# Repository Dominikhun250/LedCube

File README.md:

# LedCube
Self made pcb for a small cube lamp. Where you can set the color of the leds & the lamp.
Its a DIY project.

## Screenshots

## Credits
Original project: [AirCube](https://github.com/StuckAtPrototype/AirCube)
Pcb & Case made by: [Dominikhun250](https://github.com/Dominikhun250)

## License

[Apache License](https://github.com/Dominikhun250/LedCube/blob/main/LICENSE)

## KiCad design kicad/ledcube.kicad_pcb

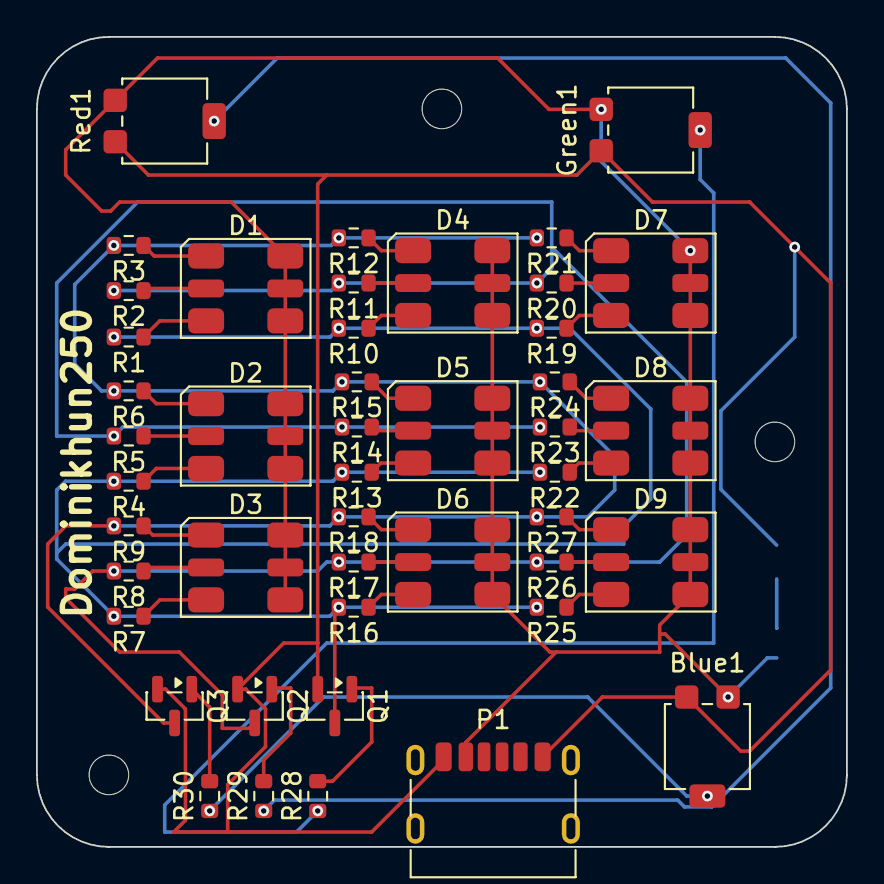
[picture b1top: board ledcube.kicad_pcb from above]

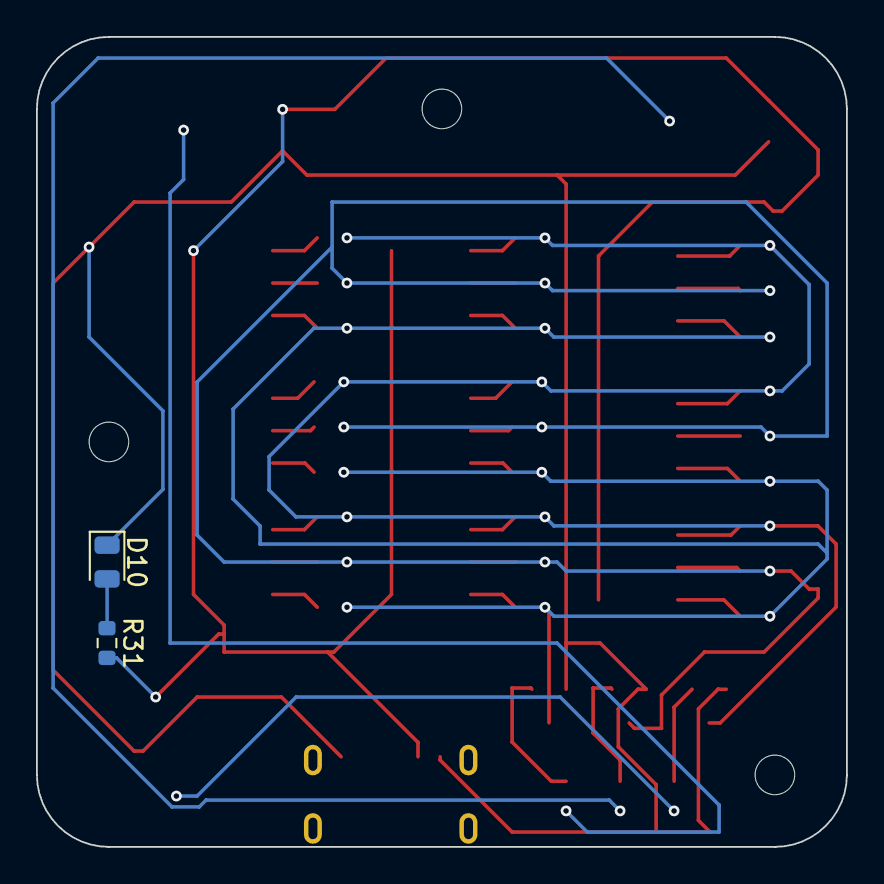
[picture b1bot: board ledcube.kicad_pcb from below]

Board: 2 copper layers, 45.0 x 45.0 mm, 48 parts (2 on the bottom side), 39 nets.

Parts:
Blue1: R_Potentiometer_Trim; Potentiometer_Bourns_3314G_Vertical
D1, D2, D3, D4, D5, D6, D7, D8, D9: Inolux_IN-P55TATRGB; LED_Inolux_IN-P55TATRGB_PLCC6_5.0x5.5mm_P1.8mm
D10: LED; LED_0805_2012Metric
Green1: R_Potentiometer_Trim; Potentiometer_Bourns_3314G_Vertical
P1: USB_C_Plug_USB2.0; USB_C_Receptacle_HRO_TYPE-C-31-M-17
Q1, Q2, Q3: BC847; SOT-23
R1, R3, R4, R6, R7, R9, R10, R12, R13, R15, R16, R18, R19, R21, R22, R24, R25, R27: 100R; R_0603_1608Metric
R2, R5, R8, R11, R14, R17, R20, R23, R26, R31: 150R; R_0603_1608Metric
R28, R29, R30: 1000R; R_0603_1608Metric
Red1: R_Potentiometer_Trim; Potentiometer_Bourns_3314G_Vertical

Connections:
unnamed: Blue1.2, R30.1
unnamed: Blue1.1, D1.4 (AG), D1.5 (AR), D1.6 (AB), D2.4 (AG), D2.5 (AR), D2.6 (AB), D3.4 (AG), D3.5 (AR), D3.6 (AB), D4.4 (AG), D4.5 (AR), D4.6 (AB), D5.4 (AG), D5.5 (AR), D5.6 (AB), D6.4 (AG), D6.5 (AR), D6.6 (AB), D7.4 (AG), D7.5 (AR), D7.6 (AB), D8.4 (AG), D8.5 (AR), D8.6 (AB), D9.4 (AG), D9.5 (AR), D9.6 (AB), Green1.1, P1.A9 (VBUS), P1.B9 (VBUS), R31.2, Red1.1
unnamed: D1.1 (KB), R3.1
unnamed: D1.3 (KG), R1.1
unnamed: D1.2 (KR), R2.1
unnamed: D2.1 (KB), R6.1
unnamed: D2.3 (KG), R4.1
unnamed: D2.2 (KR), R5.1
unnamed: D3.1 (KB), R9.1
unnamed: D3.3 (KG), R7.1
unnamed: D3.2 (KR), R8.1
unnamed: D4.1 (KB), R12.1
unnamed: D4.3 (KG), R10.1
unnamed: D4.2 (KR), R11.1
unnamed: D5.1 (KB), R15.1
unnamed: D5.3 (KG), R13.1
unnamed: D5.2 (KR), R14.1
unnamed: D6.1 (KB), R18.1
unnamed: D6.3 (KG), R16.1
unnamed: D6.2 (KR), R17.1
unnamed: D7.1 (KB), R21.1
unnamed: D7.3 (KG), R19.1
unnamed: D7.2 (KR), R20.1
unnamed: D8.1 (KB), R24.1
unnamed: D8.3 (KG), R22.1
unnamed: D8.2 (KR), R23.1
unnamed: D9.1 (KB), R27.1
unnamed: D9.3 (KG), R25.1
unnamed: D9.2 (KR), R26.1
unnamed: D10.2 (A), R31.1
unnamed: Blue1.3, D10.1 (K), Green1.3, P1.A12 (GND), P1.B12 (GND), Q1.2 (E), Q2.2 (E), Q3.2 (E), Red1.3
unnamed: Green1.2, R28.1
unnamed: Q1.1 (B), R28.2
unnamed: Q1.3 (C), R1.2, R4.2, R7.2, R10.2, R13.2, R16.2, R19.2, R22.2, R25.2
unnamed: Q2.1 (B), R29.2
unnamed: Q2.3 (C), R2.2, R5.2, R8.2, R11.2, R14.2, R17.2, R20.2, R23.2, R26.2
unnamed: Q3.1 (B), R30.2
unnamed: Q3.3 (C), R3.2, R6.2, R9.2, R12.2, R15.2, R18.2, R21.2, R24.2, R27.2
unnamed: R29.1, Red1.2
